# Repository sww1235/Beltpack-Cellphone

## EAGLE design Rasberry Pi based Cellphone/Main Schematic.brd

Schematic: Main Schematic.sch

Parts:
5VBOOST: Value; RSA0016B
ADC/DAC: SGTL5000_32QFN; QFN32
BATT: JST_2PIN-SMT-RA; JST-PH-2-SMT-RA
BATTERY_CHARGER: MCP73871-2CCI/ML; QFN50P400X400X100-21N
C1: 1uF; C0402
C2: 4700uF/10V; R/2012-12R
C3, C16, C49, C50, C51, C52: 10uF/6.3V; R/2012-12R
C4: 10uF/10V; C0402K
C5, C6: 10uF; C0402K
C7: 01uF; C0402K
C8: 2.2uF; C0402K
C9, C10, C21, C22: 100uF; C0402K
C11, C12, C13, C18, C23, C24, C25, C28, C29, C30, C53, C54, C55, C56, C57, C58: 0.1uF/16V; R/2012-12R
C14, C15: 560pF/50V; R/2012-12R
C17, C33: 22uF/6.3V; R/2012-12R
C19, C31, C32, C34, C39, C40, C41, C42: 1uF; C0402K
C20: 1uF/6.3V; R/2012-12R
C26, C27: 8pF/50V; R/2012-12R
C35, C36, C37, C38, C43, C44: 10uF; R/2012-12R
C45, C46, C47, C48: 10nF/25V; C0402
C59, C61, C62, C63, C69, C71, C72, C73, C74, C79, C81, C82, C83, C84, C89, C91, C92, C93, C98, C99, C100, C101, C102, C104, C105, C106, C107, C108, C109, C110, C111, C112, C117, C118, C119, C120, C121, C122, C123, C124, C125, C126, C127: 0.1uF; C0402
C60, C67, C70, C75, C78, C80, C85, C88, C90, C94, C95, C96, C97, C103, C113, C114, C115, C116: 0.001uF; C0402
C66, C76, C86: 1.0uF; C0402
C68, C77, C87: 0.01uF; C0402
CHRG/LBO: ORANGE; CHIP-LED0603
D1, D2: DIODESOD-123; SOD-123
D3: RB521CS-30; SMB
DONE: GREEN; CHIP-LED0603
ETHERNET: EZG-2K-308 (Cat6A Rated); EZG-1B-1K-310
EXT_POWER_IN: EZG-2K-302; EZG-2B-2K-302
EXT_RADIO_INTERFACE: EZG-0K-309; EZG-0B-0K-309
GPIOA: EZG-2K-314; EZG-2B-2K-314
GPIOB: EZG-2K-314; EZG-2B-2K-314
HDMI: 47630-1012
HEADSET: EZG-2K-305; EZG-2B-2K-305
J1: Main B2B Header; DF40C-80DS
J2: Second B2B Header; DF40C-80DS
J3: Third B2B Header; DF40C-70DS
L1: 6.8uH; L2825P
L2: 1.5uH; L2825P
L3: BLM15PX121SN1; 0402
L4, L5, L6, L7, L8, L10, L11: 1000@100MHz; FB402
LT1085: 5v; DDPAK-3
MICRO_SD: MICROSD
MSATA: 679105700
ON/OFF?: Potential Location for On Off Switch; EG1218
PCIE1, PCIE2: 679105700
PWR: RED; CHIP-LED0603
Q1: 20V P-Channel Mosfet; SOT-23
Q2: 12MHz; CTS406
R1: 270K; M0805
R2, R6: 100K; M0805
R3, R4, R5, R8, R9, R10, R13: 1K; M0805
R7: 2K; M0805
R11: 1.87M; M0805
R12: 200K; M0805
R14: 73.2K 1%; M0805
R15: 24.0K 1%; M0805
R16: 10k; M0805
R17, R18, R19, R20, R22: 2.2k; M0805
R21: 1kΩ; M0805
RESET: SPST_TACT-KMR2; KMR2
RN1: 1.5kΩ; RN8P-4R-CRA06S
RT1, RT3, RT4, RT5, RT6: 2.2K; M0805
RT2: 150K; M0805
RT7: 10K; M0805
RT8: 649; M0805
RT9: 2.2Ω; M0805
RT10, RT11: 22Ω; M0805
RT12: 1MΩ; M0805
RT13, RT14, RT17, RT18, RT21, RT22: 20Ω; M0805
RT15, RT16, RT19, RT20, RT23, RT24: 49.9Ω; M0805
RT25, RT26, RT27: 4.7kΩ; M0805
RT28: 1.6kΩ; M0805
SD2_VSELECT: 741G53DCT; DCT_R-PDSO-G8
SW1, SW2, SW3: SPST_TACT-KMR2; KMR2
THERM: 1X2-3.5MM
U7: XIO3130_ZHC_196; ZHC196
U$1: USB-PWR; USB-MINIB-THM-MOLEX-PWRONLY
U$2: 1V8 Regulator; SOT95P237X112-3N
U$3, U$4, U$5: ESD7004; UDFN10
U$6: MCP1702T-1502E/CB; SOT95P255X145-3N
U$7: MCP1700T-1502E/TT; SOT95P237X112-3N
UART_BUF_0, UART_BUF_1, UART_BUF_2: NLX2G16; UDFN6
USBCON_1: USB_1; PN87520
USBCON_OTG: USB_OTG; PN87520
USB_AUDIO_CODEC: PCM2904DB; SSOP28DB
USB_CURR_LIM: MIC2026-1YM; SOIC8
USB_HUB: USB Hub; TQFP48_7X7
VREG_1: +5V -> 3V2; SOP08
X1, X3: 5036-008-210-862; 5036_008_210_862

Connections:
1V5: C52.+, C59.1, C69.1, C79.1, C89.1, C102.1, C104.1, C105.1, C106.1, C107.1, C108.1, C109.1, C110.1, C111.1, C112.1, C113.1, C114.1, C115.1, C116.1, C117.1, C118.1, C119.1, C120.1, C121.1, C122.1, C123.1, C124.1, C125.1, C126.1, C127.1, L4.1, L5.1, L6.1, L7.1, L8.1, PCIE1.6, PCIE1.28, PCIE1.48, PCIE2.6, PCIE2.28, PCIE2.48, R18.2, U7.A4 (VDD15_2), U7.A13 (RSVD_3), U7.B2 (VDD15_3), U7.B3 (VDD15_4), U7.B7 (VDD15_5), U7.B10 (VDD15_7), U7.B12 (RSVD), U7.C5 (VDD15_6), U7.C11 (VDD15_8), U7.C13 (VDD15_9), U7.C14 (VDD15_10), U7.E13 (VDD15_11), U7.F1 (VDD15_7), U7.F2 (VDD15_8), U7.G13 (VDD15_12), U7.H3 (VDD15_9), U7.K4 (VDD15), U7.L14 (VDD15_13), U7.M1 (VDD15_2), U7.M2 (VDD15_3), U7.M11 (VDD15_14), U7.M12 (VDD15_15), U7.N8 (VDD15_4), U7.N10 (VDD15_16), U7.N13 (VDD15_17), U7.N14 (VDD15_18), U7.P3 (VDD15_5), U7.P4 (VDD15_6), U7.P14 (VDD15), U$7.2 (VOUT)
1V8: C18.+, SD2_VSELECT.6 (Y2), U$2.2 (VOUT)
3V2: ADC/DAC.5 (VDDA), ADC/DAC.20 (VDDIO), C12.-, C17.+, C23.-, C49.+, C51.+, C74.1, C84.1, C94.1, C95.1, C96.1, C97.1, C98.1, C99.1, C100.1, C101.1, GPIOA.1, GPIOB.1, J1.P$63, J1.P$65, J1.P$67, J1.P$69, L2.2, L3.1, L10.1, L11.1, MSATA.2, MSATA.24, MSATA.39, MSATA.41, MSATA.52, PCIE1.2, PCIE1.24, PCIE1.39, PCIE1.41, PCIE1.52, PCIE2.2, PCIE2.24, PCIE2.39, PCIE2.41, PCIE2.52, Q1.2 (S), R14.1, R16.2, R19.1, R20.1, R21.2, R22.1, RT5.2, SD2_VSELECT.7 (Y1), SD2_VSELECT.8 (VCC), U7.A3 (VDD33_2), U7.A11 (VDD33_4), U7.B4 (VDD33), U7.D4 (RSVD), U7.D12 (VDD33_5), U7.K12 (VDD33_6), U7.M4 (VDD33_2), U7.N1 (VDD33_3), U7.P11 (VDD33), U$2.3 (VIN), U$6.3 (VIN), U$7.3 (VIN), UART_BUF_0.P$5 (VCC), UART_BUF_1.P$5 (VCC), UART_BUF_2.P$5 (VCC), USB_HUB.23 (FIX_PORT4), USB_HUB.34 (VCC_D), USB_HUB.37 (SELFPWR), USB_HUB.38 (VCC_D_2)
12C3_SDA: GPIOB.3
+5V: 5VBOOST.1 (VOUT_2), 5VBOOST.15 (VOUT_3), 5VBOOST.16 (VOUT), C3.+, C8.1, C9.1, C10.1, C16.+, C33.+, C34.1, GPIOA.2, GPIOB.2, HDMI.P$18, J1.P$71, J1.P$73, J1.P$75, J1.P$77, J1.P$79, R11.2, RT9.2, USB_CURR_LIM.7 (IN), VREG_1.4 (VIN)
AGNDX: USB_AUDIO_CODEC.22 (AGNDX)
AUD5_RXD: ADC/DAC.25 (I2S_DOUT), J2.P$57
AUD5_TXC: ADC/DAC.24 (I2S_SCLK), J2.P$51
AUD5_TXD: ADC/DAC.26 (I2S_DIN), J2.P$53
AUD5_TXFS: ADC/DAC.23 (I2S_LRCLK), J2.P$55
BOOT_MODE0: J3.P$3
BOOT_MODE1: J3.P$5
CCM_CLKO1: ADC/DAC.21 (SYS_MCLK), J2.P$59
CCM_CLKO2: J2.P$63
CLK1_N: C57.-, J2.P$3
CLK1_P: C58.-, J2.P$1
CSI_CLK0P: J2.P$13
CSI_D0M: J2.P$8
CSI_D0P: J2.P$10
CSI_D1M: J2.P$14
CSI_D1P: J2.P$16
CSI_D2M: J2.P$20
CSI_D2P: J2.P$22
CSI_D3M: J2.P$26
CSI_D3P: J2.P$28
DI1_D0_CS: J3.P$45
DI1_D1_CS: J3.P$49
DI1_DISP_CLK: J3.P$54
DI1_PIN01: J3.P$53
DI1_PIN02: J3.P$41
DI1_PIN03: J3.P$51
DI1_PIN15: J3.P$43
DISP1_DATA00: EXT_RADIO_INTERFACE.3, J1.P$66
DISP1_DATA01: EXT_RADIO_INTERFACE.2, J1.P$60
DISP1_DATA02: GPIOB.8, J1.P$56
DISP1_DATA03: GPIOB.9, J1.P$54
DISP1_DATA04: GPIOB.10, J1.P$64
DISP1_DATA05: J1.P$62, RT28.2, U7.B1 (*UP_PERST)
DISP1_DATA06: GPIOB.11, J1.P$58
DISP1_DATA07: J3.P$70
DISP1_DATA08: J3.P$55
DISP1_DATA09: J3.P$60
DISP1_DATA10: J3.P$57
DISP1_DATA11: J3.P$68
DISP1_DATA12: J3.P$59
DISP1_DATA13: J3.P$64
DISP1_DATA14: J3.P$63
DISP1_DATA15: J3.P$62
DISP1_DATA16: J3.P$66
DISP1_DATA17: J3.P$69
DISP1_DATA18: J3.P$56
DISP1_DATA19: J3.P$67
DISP1_DATA20: J3.P$58
DISP1_DATA21: J3.P$40
DISP1_DATA22: J3.P$61
DISP1_DATA23: J3.P$65
DN1_PERST: PCIE1.22, RT27.2, U7.B5 (*DN1_PERST)
DN2_PERST: PCIE2.22, RT25.2, U7.A2 (*DN2_PERST)
DN3_PERST: RT26.2, U7.A1 (*DN3_PERST)
DSI_CLK0M: J2.P$44
DSI_CLK0P: J2.P$46
DSI_D0M: J2.P$38
DSI_D0P: J2.P$40
DSI_D1M: J2.P$32
DSI_D1P: J2.P$34
ECSPI2_MISO: GPIOA.4, J1.P$45
ECSPI2_MOSI: GPIOA.3, J1.P$47
ECSPI2_SCLK: GPIOA.5, J1.P$49
ECSPI2_SS0: GPIOA.6, J1.P$32
ECSPI2_SS1: GPIOA.7, J1.P$34
EIM_WAIT: J3.P$1
ETH_TCT: C1.1, ETHERNET.9, ETHERNET.10, J1.P$29
GNDC: C1.2
HDMI_CEC_C: D3.C, HDMI.P$13, U$5.P$10
HDMI_CLKM: J2.P$39, U$4.P$5
HDMI_CLKP: J2.P$37, U$4.P$4
HDMI_D0M: J2.P$33, U$4.P$2
HDMI_D0P: J2.P$31, U$4.P$1
HDMI_D1M: J2.P$27, U$3.P$5
HDMI_D1P: J2.P$25, U$3.P$4
HDMI_D2M: J2.P$21, U$3.P$2
HDMI_D2P: J2.P$19, U$3.P$1
HDMI_HPD: J2.P$49, U$5.P$5
HDMI_HPD_C: HDMI.P$19, U$5.P$6
HDMI_SCL_C: HDMI.P$15, U$5.P$9
HDMI_SDA_C: HDMI.P$16, U$5.P$7
HDMI_TX_CEC_LINE: J2.P$43, U$5.P$1
HDMI_TX_DDC_SCL: J2.P$45, U$5.P$2
HDMI_TX_DDC_SDA: J2.P$47, U$5.P$4
I2C1_SCL: ADC/DAC.29 (CTRL_CLK), J1.P$53, MSATA.30, U7.B14 (SCL)
I2C1_SDA: ADC/DAC.27 (CTRL_DATA), J1.P$51, MSATA.32, U7.D13 (SDA)
I2C3_SCL: GPIOB.4, J1.P$31
I2C3_SDA: J1.P$33
LED_10_100_LED_1000: J1.P$25
LED_ACT: J1.P$27
LOWVOLTAGE: 5VBOOST.12 (LBO)
LVDS0_CLK_N: J2.P$78
LVDS0_CLK_P: J2.P$80
LVDS0_TX0_N: J2.P$60
LVDS0_TX0_P: J2.P$62
LVDS0_TX1_N: J2.P$66
LVDS0_TX1_P: J2.P$68
LVDS0_TX2_N: J2.P$72
LVDS0_TX2_P: J2.P$74
LVDS0_TX3_N: J2.P$79
LVDS0_TX3_P: J2.P$77
MDI_TRXN0: ETHERNET.2, J1.P$19
MDI_TRXN1: ETHERNET.4, J1.P$13
MDI_TRXN2: ETHERNET.6, J1.P$7
MDI_TRXN3: ETHERNET.8, J1.P$1
MDI_TRXP0: ETHERNET.1, J1.P$21
MDI_TRXP1: ETHERNET.3, J1.P$15
MDI_TRXP2: ETHERNET.5, J1.P$9
MDI_TRXP3: ETHERNET.7, J1.P$3
MIC_IN: C24.-, HEADSET.2, RT6.1
MLB_CN: J3.P$19
MLB_CP: J3.P$17
MLB_DN: J3.P$27
MLB_DP: J3.P$25
MLB_SN: J3.P$23
MLB_SP: J3.P$21
MSATA_DISABLE: MSATA.20, PCIE1.20, PCIE2.20, R16.1
MUTE/PWR_DOWN: RN1.5 (2), RN1.6 (2), RN1.7 (2), USB_AUDIO_CODEC.28 (!SSPND)
MX6_ONOFF: J3.P$13
unnamed: D1.A, EXT_POWER_IN.2
unnamed: D1.C, LT1085.3 (VIN)
unnamed: BATTERY_CHARGER.6 (*PG), PWR.C
unnamed: D2.A, U$1.VBUS
unnamed: BATTERY_CHARGER.2 (VPCC), R1.1, R2.2
unnamed: PWR.A, R3.2
unnamed: L2.1, VREG_1.5 (LX)
unnamed: CHRG/LBO.A, R5.2
unnamed: BATTERY_CHARGER.7 (STAT2), DONE.C
unnamed: DONE.A, R4.2
unnamed: BATTERY_CHARGER.8 (STAT1/*LBO), CHRG/LBO.C
unnamed: BATT.1 (2), BATTERY_CHARGER.14 (VBAT), BATTERY_CHARGER.15 (VBAT_2), BATTERY_CHARGER.16 (VBAT_SENSE), C6.1
unnamed: BATTERY_CHARGER.12 (PROG3), R6.2
unnamed: BATTERY_CHARGER.13 (PROG1), R7.2
unnamed: 5VBOOST.11 (EN), ON/OFF?.P
unnamed: BATTERY_CHARGER.5 (THERM), R8.2
unnamed: R8.1, RT2.2, THERM.1
unnamed: ADC/DAC.30 (VDDD), C11.-
unnamed: R14.2, R15.1, VREG_1.7 (FB)
unnamed: 5VBOOST.9 (LBI), R9.2, R10.1
unnamed: ADC/DAC.15 (MIC), C24.+
unnamed: 5VBOOST.3 (SW_2), 5VBOOST.4 (SW), L1.2
unnamed: 5VBOOST.14 (FB), R11.1, R12.2
unnamed: ADC/DAC.10 (VAG), C13.-
unnamed: C15.+, VREG_1.2 (SS)
unnamed: D3.A, RT5.1
unnamed: R13.1, VREG_1.1 (COMP)
unnamed: C14.+, R13.2
unnamed: ADC/DAC.2 (HP_R), C21.1
unnamed: ADC/DAC.6 (HP_L), C22.1
unnamed: ADC/DAC.16 (MIC_BIAS), C25.-, RT6.2
unnamed: C40.1, USB_AUDIO_CODEC.23 (VCCXI)
unnamed: C41.1, USB_AUDIO_CODEC.19 (VCCP2I)
unnamed: RT8.1, USB_HUB.11 (RREF)
unnamed: RT7.1, USB_HUB.39 (GANG)
unnamed: RT9.1, USB_AUDIO_CODEC.3 (VBUS)
unnamed: RT11.1, USB_AUDIO_CODEC.2 (D-)
unnamed: RT10.1, USB_AUDIO_CODEC.1 (D+)
unnamed: C33.-, USB_CURR_LIM.6 (GND)
unnamed: C35.+, USB_AUDIO_CODEC.10 (VCCCI)
unnamed: C36.+, EXT_RADIO_INTERFACE.4, EXT_RADIO_INTERFACE.7, USB_AUDIO_CODEC.14 (VCOM)
unnamed: C42.1, USB_AUDIO_CODEC.17 (VCCP1I)
unnamed: C38.+, USB_AUDIO_CODEC.12 (VINL)
unnamed: C37.+, USB_AUDIO_CODEC.13 (VINR)
unnamed: C38.-, EXT_RADIO_INTERFACE.9
unnamed: C37.-, EXT_RADIO_INTERFACE.8
unnamed: C43.-, EXT_RADIO_INTERFACE.6
unnamed: C44.-, EXT_RADIO_INTERFACE.5
unnamed: C43.+, USB_AUDIO_CODEC.15 (VOUTR)
unnamed: C44.+, USB_AUDIO_CODEC.16 (VOUTL)
unnamed: C45.1, MSATA.23
unnamed: SW3.1, SW3.3 (P1), USB_AUDIO_CODEC.5 (HID0)
unnamed: SW2.1, SW2.3 (P1), USB_AUDIO_CODEC.6 (HID1)
unnamed: RN1.2 (1), SW1.2 (S), SW1.4 (S1)
unnamed: SW1.1, SW1.3 (P1), USB_AUDIO_CODEC.7 (HID2)
unnamed: C39.1, RN1.8 (2), USB_AUDIO_CODEC.8 (SEL0), USB_AUDIO_CODEC.9 (SEL1), USB_AUDIO_CODEC.27 (VDDI)
unnamed: RN1.3 (1), SW2.2 (S), SW2.4 (S1)
unnamed: RN1.4 (1), SW3.2 (S), SW3.4 (S1)
unnamed: C46.1, MSATA.25
unnamed: C47.1, MSATA.31
unnamed: C48.1, MSATA.33
unnamed: C54.-, PCIE2.31
unnamed: C53.-, PCIE2.33
unnamed: C56.-, PCIE1.31
unnamed: C55.-, PCIE1.33
unnamed: C57.+, U7.L2 (UP_REFCKIN)
unnamed: C58.+, U7.L1 (UP_REFCKIP)
NVCC_SD2: C19.1, J1.P$61, SD2_VSELECT.1 (COM)
PCIE_RXM: J2.P$2, U7.J2 (UP_PERN)
PCIE_RXM1: PCIE1.23, U7.B6 (DN1_PERN)
PCIE_RXM2: PCIE2.23, U7.F14 (DN2_PERN)
PCIE_RXM3: U7.P9 (DN3_PERN)
PCIE_RXP: J2.P$4, U7.J1 (UP_PERP)
PCIE_RXP1: PCIE1.25, U7.A6 (DN1_PERP)
PCIE_RXP2: PCIE2.25, U7.F13 (DN2_PERP)
PCIE_RXP3: U7.N9 (DN3_PERP)
PCIE_TXM: J2.P$7, U7.G2 (UP_PETN)
PCIE_TXM1: C56.+, U7.B8 (DN1_PETN)
PCIE_TXM2: C54.+, U7.H14 (DN2_PETN)
PCIE_TXM3: U7.P7 (DN3_PETN)
PCIE_TXP: J2.P$9, U7.A8 (DN1_PETP), U7.G1 (UP_PETP)
PCIE_TXP1: C55.+
PCIE_TXP2: C53.+, U7.H13 (DN2_PETP)
PCIE_TXP3: U7.N7 (DN3_PETP)
PE: 5VBOOST.5 (PGND_2), 5VBOOST.6 (PGND_3), 5VBOOST.7 (PGND), 5VBOOST.10 (SYNC), 5VBOOST.13 (GND), 5VBOOST.17 (PAD), ADC/DAC.1 (GND), ADC/DAC.3 (GND2), ADC/DAC.7 (AGND), ADC/DAC.31 (CTRL_ADR0_CS), ADC/DAC.32 (CTRL_MODE), ADC/DAC.EXP (GND), BATT.2 (1), BATTERY_CHARGER.10 (VSS), BATTERY_CHARGER.11 (VSS_2), BATTERY_CHARGER.21 (EP), C2.-, C3.-, C4.2, C5.2, C6.2, C7.2, C8.2, C9.2, C10.2, C11.+, C12.+, C13.+, C14.-, C15.-, C16.-, C17.-, C18.-, C19.2, C20.-, C23.+, C25.+, C26.-, C27.-, C28.-, C29.-, C30.-, C31.2, C32.2, C34.2, C35.-, C36.-, C39.2, C40.2, C41.2, C42.2, C49.-, C50.-, C51.-, C52.-, C59.2, C60.2, C61.2, C62.2, C63.2, C66.2, C67.2, C68.2, C69.2, C70.2, C71.2, C72.2, C73.2, C74.2, C75.2, C76.2, C77.2, C78.2, C79.2, C80.2, C81.2, C82.2, C83.2, C84.2, C85.2, C86.2, C87.2, C88.2, C89.2, C90.2, C91.2, C92.2, C93.2, C94.2, C95.2, C96.2, C97.2, C98.2, C99.2, C100.2, C101.2, C102.2, C103.2, C104.2, C105.2, C106.2, C107.2, C108.2, C109.2, C110.2, C111.2, C112.2, C113.2, C114.2, C115.2, C116.2, C117.2, C118.2, C119.2, C120.2, C121.2, C122.2, C123.2, C124.2, C125.2, C126.2, C127.2, EXT_POWER_IN.1, EXT_RADIO_INTERFACE.1, GPIOA.14, GPIOB.14, HDMI.P$2, HDMI.P$5, HDMI.P$8, HDMI.P$11, HDMI.P$17, HEADSET.1, HEADSET.3, J1.P$2, J1.P$5, J1.P$8, J1.P$11, J1.P$14, J1.P$17, J1.P$20, J1.P$23, J1.P$26, J1.P$35, J1.P$36, J1.P$70, J1.P$72, J1.P$74, J1.P$76, J1.P$78, J1.P$80, J2.P$5, J2.P$6, J2.P$11, J2.P$12, J2.P$17, J2.P$18, J2.P$23, J2.P$24, J2.P$29, J2.P$30, J2.P$35, J2.P$36, J2.P$48, J2.P$58, J2.P$61, J2.P$64, J2.P$70, J2.P$75, J3.P$10, J3.P$16, J3.P$30, J3.P$33, J3.P$47, J3.P$52, LT1085.1 (GND), LT1085.THERM (GND), MICRO_SD.6 (VSS), MICRO_SD.MT1 (GND), MICRO_SD.MT2 (GND1), MSATA.4, MSATA.9, MSATA.15, MSATA.18, MSATA.21, MSATA.26, MSATA.27, MSATA.29, MSATA.34, MSATA.35, MSATA.37, MSATA.40, MSATA.43, MSATA.50, ON/OFF?.O, PCIE1.4, PCIE1.9, PCIE1.15, PCIE1.18, PCIE1.21, PCIE1.26, PCIE1.27, PCIE1.29, PCIE1.34, PCIE1.35, PCIE1.37, PCIE1.40, PCIE1.43, PCIE1.50, PCIE2.4, PCIE2.9, PCIE2.15, PCIE2.18, PCIE2.21, PCIE2.26, PCIE2.27, PCIE2.29, PCIE2.34, PCIE2.35, PCIE2.37, PCIE2.40, PCIE2.43, PCIE2.50, R2.1, R6.1, R7.1, R10.2, R12.1, R15.2, R17.1, R18.1, RESET.3 (P1), RT1.2, RT2.1, RT3.1, RT4.1, RT7.2, RT8.2, RT15.2, RT16.2, RT19.2, RT20.2, RT23.2, RT24.2, RT25.1, RT26.1, RT27.1, RT28.1, SD2_VSELECT.2 (INH), SD2_VSELECT.3 (GND), SD2_VSELECT.4 (GND), THERM.2, U7.A5 (VSSA_2), U7.A10 (VSSA_8), U7.C4 (RSVD_2), U7.C7 (VSSA_3), U7.C8 (VSSA_4), U7.C9 (VSSA_5), U7.C10 (DN1_DPSTRP), U7.D1 (VSSD_REF), U7.D5 (VSS_2), U7.D6 (VSS_3), U7.D10 (VSS_3), U7.D11 (VSS_4), U7.E4 (VSSA_REF), U7.E5 (VSS_4), U7.E6 (VSS_5), U7.E7 (VSS_6), U7.E8 (VSS_7), U7.E9 (VSS_8), U7.E10 (VSS_5), U7.E11 (VSS_6), U7.E12 (VSS_7), U7.E14 (VSSA_9), U7.F5 (VSS_9), U7.F6 (VSS_10), U7.F7 (VSS_11), U7.F8 (VSS_12), U7.F9 (VSS_13), U7.F10 (VSS_8), U7.F11 (VSSA_10), U7.F12 (VSSA_11), U7.G3 (VSSA_6), U7.G5 (VSS_14), U7.G6 (VSS_15), U7.G7 (VSS_16), U7.G8 (VSS_17), U7.G9 (VSS_18), U7.G10 (VSS_9), U7.G14 (VSSA_12), U7.H1 (VSSA_7), U7.H5 (VSS_19), U7.H6 (VSS_20), U7.H7 (VSS_21), U7.H8 (VSS_22), U7.H9 (VSS_23), U7.H10 (VSS_10), U7.H12 (VSSA_13), U7.J5 (VSS_24), U7.J6 (VSS_25), U7.J7 (VSS_26), U7.J8 (VSS_27), U7.J9 (VSS_28), U7.J10 (VSS_11), U7.J13 (VSSA_14), U7.K1 (VSSA), U7.K2 (VSS_29), U7.K5 (VSS_30), U7.K6 (VSS_31), U7.K7 (VSS_32), U7.K8 (VSS_33), U7.K9 (VSS_34), U7.K10 (VSS_12), U7.K11 (VSS_13), U7.K13 (VSSA_15), U7.L4 (VSS_35), U7.L5 (VSS), U7.L9 (VSSA_2), U7.L10 (VSS_14), U7.L11 (VSS), U7.L13 (DN2_DPSTRP), U7.M5 (VSS_2), U7.M7 (VSSA_3), U7.M9 (VSSA_4), U7.N4 (DN3_DPSTRP), U7.N5 (VSSA_5), U7.N6 (VSSA_6), U7.P1 (RSVD_2), U7.P8 (VSSA_7), U7.P10 (VSSA), U$1.GND, U$2.1 (GND), U$3.P$3 (GND), U$3.P$8 (GND2), U$4.P$3 (GND), U$4.P$8 (GND2), U$5.P$3 (GND), U$5.P$8 (GND2), U$6.1 (GND), U$7.1 (GND), UART_BUF_0.P$2 (GND), UART_BUF_1.P$2 (GND), UART_BUF_2.P$2 (GND), USBCON_1.4, USBCON_OTG.4, USB_AUDIO_CODEC.4 (DGNDU), USB_AUDIO_CODEC.11 (AGNDC), USB_AUDIO_CODEC.18 (AGNDP), USB_AUDIO_CODEC.24 (TEST0), USB_AUDIO_CODEC.26 (DGND), USB_HUB.2 (GND), USB_HUB.8 (GND_2), USB_HUB.13 (GND_3), USB_HUB.20 (GND_4), VREG_1.P$1 (GND), X1.C3, X3.C3
PMIC_ON_REQ: J3.P$15
PMIC_STBY_REQ: J3.P$9
POR_B: J2.P$65, MSATA.22, RESET.4 (S1), USB_HUB.26 (RESET#)
PWM1_OUT: J1.P$68
PWM2_OUT: J1.P$41, Q1.1 (G), RT3.2
PWM3_OUT: J1.P$55
PWM4_OUT: J1.P$57
REFCLKN_1: PCIE1.11, RT14.2, RT16.1
REFCLKN_1_R: RT14.1, U7.B9 (DN1_REFCK_ON)
REFCLKN_2: PCIE2.11, RT22.2, RT24.1
REFCLKN_2_R: RT22.1, U7.J14 (DN2_REFCKON)
REFCLKN_3: RT18.2, RT20.1
REFCLKN_3_R: RT18.1, U7.P6 (DN3_REFCKON)
REFCLKP_1: PCIE1.13, RT13.2, RT15.1
REFCLKP_1_R: RT13.1, U7.A9 (DN1_REFCK_OP)
REFCLKP_2: PCIE2.13, RT21.2, RT23.1
REFCLKP_2_R: RT21.1, U7.K14 (DN2_REFCKOP)
REFCLKP_3: RT17.2, RT19.1
REFCLKP_3_R: RT17.1, U7.P5 (DN3_REFCKOP)
RXD0: GPIOA.9, R20.2, UART_BUF_0.P$3 (IN_A2)
RXD1: GPIOA.11, R19.2, UART_BUF_1.P$3 (IN_A2)
RXD2: GPIOA.13, R22.2, UART_BUF_2.P$3 (IN_A2)
SATA_RXN: C46.2, J1.P$6
SATA_RXP: C45.2, J1.P$4
SATA_TXN: C47.2, J1.P$10
SATA_TXP: C48.2, J1.P$12
SD2_CD_B: J1.P$50, MICRO_SD.CD1 (CARD_DETECT), MICRO_SD.CD2 (CARD_DETECT1)
SD2_CLK: J1.P$38, MICRO_SD.5 (SCLK)
SD2_CMD: J1.P$40, MICRO_SD.3 (DATA_IN)
SD2_DATA0: J1.P$42, MICRO_SD.7 (DATA_OUT)
SD2_DATA1: J1.P$44, MICRO_SD.8 (DAT1)
SD2_DATA2: J1.P$46, MICRO_SD.1 (DAT2)
SD2_DATA3: J1.P$48, MICRO_SD.2 (CS)
SD2_VSELECT: J2.P$73, RT1.1, SD2_VSELECT.5 (A)
SD3_CLK: GPIOB.6, J1.P$37
SD3_CMD: GPIOB.7, J1.P$39
SD3_DATA0: J3.P$24
SD3_DATA1: J3.P$22
SD3_DATA2: J3.P$20
SD3_DATA3: J3.P$18
SD3_DATA4: J3.P$8
SD3_DATA5: J3.P$6
SD3_DATA6: J3.P$4
SD3_DATA7: J3.P$2
SD3_RST: J3.P$26
SD3_VSELECT: J3.P$28
SD4_CLK: J3.P$32
SD4_CMD: J3.P$34
SD4_DATA0: J3.P$36
SD4_DATA3: J3.P$38
SPDIF_IN: J3.P$35
SPDIF_OUT: J2.P$50
STEREO_OUT_L: C22.2, HEADSET.4
STEREO_OUT_R: C21.2, HEADSET.5
TAMPER: J3.P$7
TMDS0+_C: HDMI.P$7, U$4.P$10
TMDS0-_C: HDMI.P$9, U$4.P$9
TMDS1+_C: HDMI.P$4, U$3.P$7
TMDS1-_C: HDMI.P$6, U$3.P$6
TMDS2+_C: HDMI.P$1, U$3.P$10
TMDS2-_C: HDMI.P$3, U$3.P$9
TMDSCLK+_C: HDMI.P$10, U$4.P$7
TMDSCLK-_C: HDMI.P$12, U$4.P$6
TXD0: GPIOA.8, UART_BUF_0.P$6 (OUT_Y1)
TXD1: GPIOA.10, UART_BUF_1.P$6 (OUT_Y1)
TXD2: GPIOA.12, UART_BUF_2.P$6 (OUT_Y1)
UART1_RX_DATA: J2.P$54, UART_BUF_0.P$4 (OUT_Y2)
UART1_TX_DATA: J2.P$52, UART_BUF_0.P$1 (IN_A1)
UART2_CTS_B: J3.P$48
UART2_RTS_B: J3.P$50
UART2_RX_DATA: J3.P$44, UART_BUF_1.P$4 (OUT_Y2)
UART2_TX_DATA: J3.P$46, UART_BUF_1.P$1 (IN_A1)
UART3_RX_DATA: J3.P$31, UART_BUF_2.P$4 (OUT_Y2)
UART3_TX_DATA: J3.P$29, UART_BUF_2.P$1 (IN_A1)
UIM_AUX1_1: X3.C6
UIM_AUX1_2: X1.C6
UIM_AUX2_1: X3.C8
UIM_AUX2_2: X1.C8
UIM_CLK_1: PCIE1.12, X3.C2
UIM_CLK_2: PCIE2.12, X1.C2
UIM_DATA_1: PCIE1.10, X3.C4
UIM_DATA_2: PCIE2.10, X1.C4
UIM_PWR_1: PCIE1.8, X3.C1
UIM_PWR_2: PCIE2.8, X1.C1
UIM_RST_1: PCIE1.14, X3.C5
UIM_RST_2: PCIE2.14, X1.C5
UIM_VPP_1: PCIE1.16, X3.C7
UIM_VPP_2: PCIE2.16, X1.C7
USB_H1_OC: J2.P$69
USB_H1_PWR_EN: J1.P$28, USB_CURR_LIM.4 (ENB)
USB_H1_VBUS: J1.P$52, USBCON_1.1, USB_CURR_LIM.5 (OUTB)
USB_HOST_DN: J1.P$24, USB_HUB.3 (D-)
USB_HOST_DP: J1.P$22, USB_HUB.4 (D+)
USB_HUB_DN1: USBCON_1.2, USB_HUB.5 (DD-[1])
USB_HUB_DN2: PCIE1.36, USB_HUB.9 (DD-[2])
USB_HUB_DN3: PCIE2.36, USB_HUB.17 (DD-[3])
USB_HUB_DN4: RT11.2, USB_HUB.21 (DD-[4])
USB_HUB_DP1: USBCON_1.3, USB_HUB.6 (DD+[1])
USB_HUB_DP2: PCIE1.38, USB_HUB.10 (DD+[2])
USB_HUB_DP3: PCIE2.38, USB_HUB.18 (DD+[3])
USB_HUB_DP4: RN1.1, RT10.2, USB_HUB.22 (DD+[4])
USB_OTG_CHD_B: J2.P$71
USB_OTG_DN: J1.P$18, USBCON_OTG.2
USB_OTG_DP: J1.P$16, USBCON_OTG.3
USB_OTG_ID: GPIOB.5, J2.P$56
USB_OTG_OC: J2.P$67
USB_OTG_PWR_EN: J1.P$30, USB_CURR_LIM.1 (ENA)
USB_OTG_VBUS: J1.P$43, USBCON_OTG.1, USB_CURR_LIM.8 (OUTA)
VAUX33REF: R21.1, U7.E1 (VAUX33_REF)
VBAT: 5VBOOST.8 (VBAT), BATTERY_CHARGER.1 (OUT_2), BATTERY_CHARGER.20 (OUT), C5.1, C7.1, L1.1, ON/OFF?.S, R9.1
VCC: USB_HUB.47 (VCC)
VDD15REF: C103.1, L8.2, U7.F3 (VDD15_REF)
VDD33REF: C85.1, L11.2, U7.E2 (VDD33_REF)
VDDA15_0: C60.1, C61.1, C62.1, C63.1, L4.2, U7.G4 (VDDA15_6), U7.H2 (VDDA15_7), U7.H4 (VDDA15_8), U7.J4 (VDDA15_9), U7.K3 (VDDA15_10)
VDDA15_1: C70.1, C71.1, C72.1, C73.1, L5.2, U7.A7 (VDDA15_2), U7.D7 (VDDA15_3), U7.D8 (VDDA15_4), U7.D9 (VDDA15_5)
VDDA15_2: C80.1, C81.1, C82.1, C83.1, L6.2, U7.G11 (VDDA15_4), U7.G12 (VDDA15_5), U7.H11 (VDDA15_6), U7.J11 (VDDA15_7), U7.J12 (VDDA15)
VDDA15_3: C90.1, C91.1, C92.1, C93.1, L7.2, U7.L6 (VDDA15_11), U7.L7 (VDDA15_12), U7.L8 (VDDA15), U7.M6 (VDDA15_2), U7.M8 (VDDA15_3)
VDDA33F: C75.1, L10.2, U7.J3 (VDDA33)
VDDCOMB15: C86.1, C87.1, C88.1, U7.C1 (VDD_COMB15)
VDDCOMB33: C76.1, C77.1, C78.1, U7.F4 (VDD_COMB33)
VDDCOMBIO: C66.1, C67.1, C68.1, U7.D3 (VDD_COMBIO)
VIN+5VBATT: BATTERY_CHARGER.3 (SEL), BATTERY_CHARGER.4 (PROG2), BATTERY_CHARGER.9 (*TE), BATTERY_CHARGER.17 (CE), BATTERY_CHARGER.18 (IN_2), BATTERY_CHARGER.19 (IN), C2.+, C4.1, D2.C, LT1085.2 (VOUT), R1.2, R3.1, R4.1, R5.1
V_1V5: C50.+, MSATA.6, MSATA.28, MSATA.48, R17.2, U$6.2 (VOUT)
V_3V2_FLTR: C28.+, C29.+, C30.+, C31.1, C32.1, L3.2, USB_HUB.1 (VCC_A), USB_HUB.7 (VCC_A_2), USB_HUB.12 (VCC_A_3), USB_HUB.16 (VCC_A_4), USB_HUB.19 (VCC_A_5), USB_HUB.48 (VREG)
V_SD: C20.+, MICRO_SD.4 (VDD), Q1.3 (D), RT4.2
WDOG1_B: J3.P$42
XIN: C26.+, Q2.1, RT12.1, USB_AUDIO_CODEC.21 (XTI), USB_HUB.14 (XIN)
XOUT: C27.+, Q2.3 (2), RT12.2, USB_AUDIO_CODEC.20 (XTO), USB_HUB.15 (XOUT)

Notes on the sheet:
pcie bus
msata
1x stacked USB and HDMI Digital Coax S/PDIF LEDS Various Display connectors (Maybe leave off) RTC battery HEader MIPI CSI connector?
connect 10k thermistor here
connect low voltage to microcontroller to trigger low battery shutdown
Main Power feeds are +5V and 3V2
may need amplifiers here
Connect to amplifier if needed

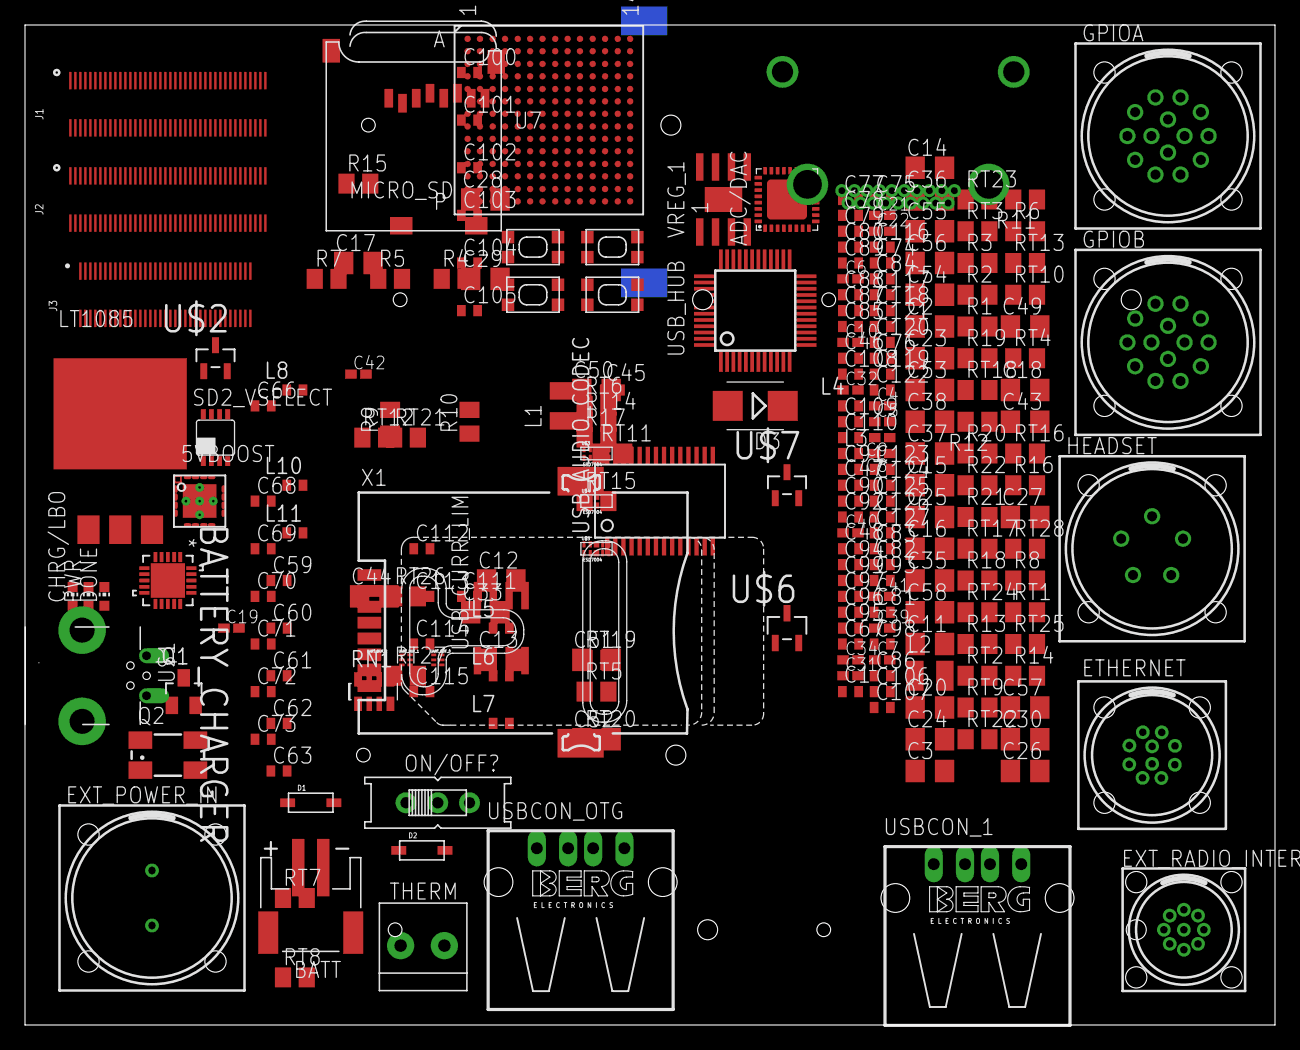
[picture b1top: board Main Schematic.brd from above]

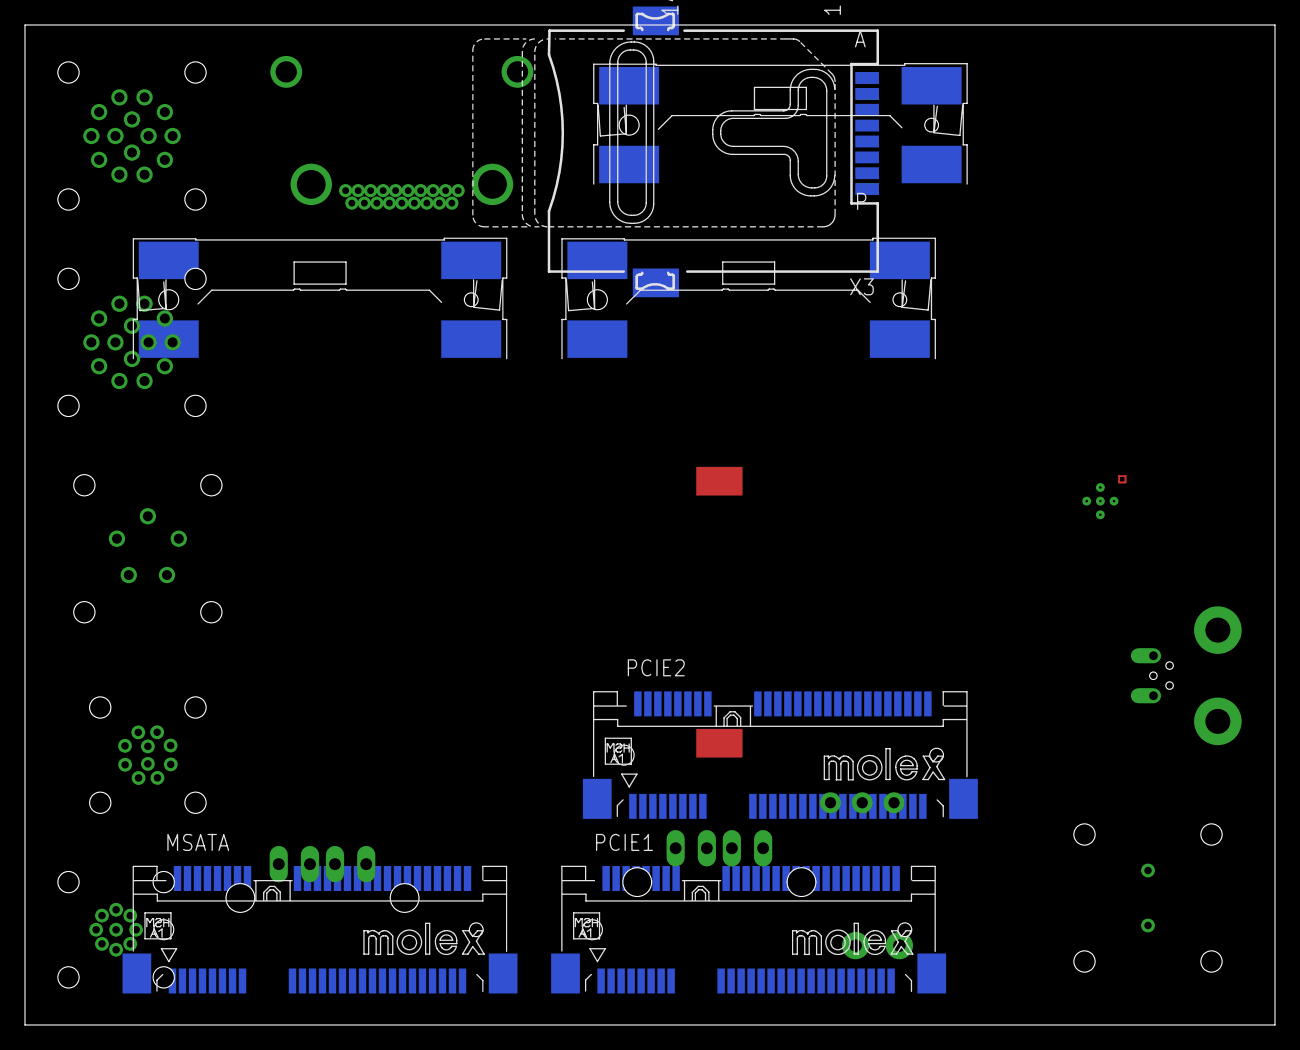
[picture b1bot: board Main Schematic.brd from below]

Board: 2 copper layers, 100.0 x 80.0 mm, 239 parts (4 on the bottom side), 232 nets, no tracks yet.

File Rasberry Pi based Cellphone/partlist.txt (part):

Partlist

Exported from Main Schematic.sch at 5/1/15 15:12

EAGLE Version 7.2.0 Copyright (c) 1988-2014 CadSoft

Assembly variant: 

Part                Value                                Device                     Package                     Library                        Sheet

5VBOOST             Value                                TPS61030RSAR               RSA0016B                    texas                          1
ADC/DAC             SGTL5000_32QFN                       SGTL5000                   QFN32                       freescale                      1
BATT                                                     JST_2PIN-SMT-RA            JST-PH-2-SMT-RA             adafruit                       1
BATTERY_CHARGER     MCP73871-2CCI/ML                     MCP73871-2CCI/ML           QFN50P400X400X100-21N       Microchip_By_element14_Batch_1 1
C1                  1uF                                  C-USC0402                  C0402                       adafruit                       1
C2                  4700uF/10V                           CPOL-USR/2012-12R          R/2012-12R                  adafruit                       1
C3                  10uF/6.3V                            CPOL-USR/2012-12R          R/2012-12R                  adafruit                       1
C4                  10uF/10V                             C-USC0402K                 C0402K                      adafruit                       1
C5                  10uF                                 C-USC0402K                 C0402K                      adafruit                       1
C6                  10uF                                 C-USC0402K                 C0402K                      adafruit                       1
C7                  01uF                                 C-USC0402K                 C0402K                      adafruit                       1
C8                  2.2uF                                C-USC0402K                 C0402K                      adafruit                       1
C9                  100uF                                C-USC0402K                 C0402K                      adafruit                       1
C10                 100uF                                C-USC0402K                 C0402K                      adafruit                       1
C11                 0.1uF/16V                            CPOL-USR/2012-12R          R/2012-12R                  adafruit                       1
C12                 0.1uF/16V                            CPOL-USR/2012-12R          R/2012-12R                  adafruit                       1
C13                 0.1uF/16V                            CPOL-USR/2012-12R          R/2012-12R                  adafruit                       1
C14                 560pF/50V                            CPOL-USR/2012-12R          R/2012-12R                  adafruit                       1
C15                 560pF/50V                            CPOL-USR/2012-12R          R/2012-12R                  adafruit                       1
C16                 10uF/6.3V                            CPOL-USR/2012-12R          R/2012-12R                  adafruit                       1
C17                 22uF/6.3V                            CPOL-USR/2012-12R          R/2012-12R                  adafruit                       1
C18                 0.1uF/16V                            CPOL-USR/2012-12R          R/2012-12R                  adafruit                       1
C19                 1uF                                  C-USC0402K                 C0402K                      adafruit                       1
C20                 1uF/6.3V                             CPOL-USR/2012-12R          R/2012-12R                  adafruit                       1
C21                 100uF                                C-USC0402K                 C0402K                      adafruit                       1
C22                 100uF                                C-USC0402K                 C0402K                      adafruit                       1
C23                 0.1uF/16V                            CPOL-USR/2012-12R          R/2012-12R                  adafruit                       1
C24                 0.1uF/16V                            CPOL-USR/2012-12R          R/2012-12R                  adafruit                       1
C25                 0.1uF/16V                            CPOL-USR/2012-12R          R/2012-12R                  adafruit                       1
C26                 8pF/50V                              CPOL-USR/2012-12R          R/2012-12R                  adafruit                       1
C27                 8pF/50V                              CPOL-USR/2012-12R          R/2012-12R                  adafruit                       1
C28                 0.1uF/16V                            CPOL-USR/2012-12R          R/2012-12R                  adafruit                       1
C29                 0.1uF/16V                            CPOL-USR/2012-12R          R/2012-12R                  adafruit                       1
C30                 0.1uF/16V                            CPOL-USR/2012-12R          R/2012-12R                  adafruit                       1
C31                 1uF                                  C-USC0402K                 C0402K                      adafruit                       1
C32                 1uF                                  C-USC0402K                 C0402K                      adafruit                       1
C33                 22uF/6.3V                            CPOL-USR/2012-12R          R/2012-12R                  adafruit                       1
C34                 1uF                                  C-USC0402K                 C0402K                      adafruit                       1
C35                 10uF                                 CPOL-USR/2012-12R          R/2012-12R                  adafruit                       1
C36                 10uF                                 CPOL-USR/2012-12R          R/2012-12R                  adafruit                       1
C37                 10uF                                 CPOL-USR/2012-12R          R/2012-12R                  adafruit                       1
C38                 10uF                                 CPOL-USR/2012-12R          R/2012-12R                  adafruit                       1
C39                 1uF                                  C-USC0402K                 C0402K                      adafruit                       1
C40                 1uF                                  C-USC0402K                 C0402K                      adafruit                       1
C41                 1uF                                  C-USC0402K                 C0402K                      adafruit                       1
C42                 1uF                                  C-USC0402K                 C0402K                      adafruit                       1
C43                 10uF                                 CPOL-USR/2012-12R          R/2012-12R                  adafruit                       1
C44                 10uF                                 CPOL-USR/2012-12R          R/2012-12R                  adafruit                       1
C45                 10nF/25V                             C-USC0402                  C0402                       adafruit                       1
C46                 10nF/25V                             C-USC0402                  C0402                       adafruit                       1
C47                 10nF/25V                             C-USC0402                  C0402                       adafruit                       1
C48                 10nF/25V                             C-USC0402                  C0402                       adafruit                       1
C49                 10uF/6.3V                            CPOL-USR/2012-12R          R/2012-12R                  adafruit                       1
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
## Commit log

2015-04-15 Adding Initial Files
2015-04-22 Adding Connectors
2015-04-22 Finished Wiring main b2b connectors
2015-04-24 Finished Power Supply and Battery Charger
2015-04-25 added audio, usband some more power stuff
2015-04-30 random commit
2015-05-01 almost finished schematic
2015-05-01 fixed some errors in schematic and made brd easier to look at
2015-07-18 adding txt version of description
2015-07-19 Create New Ideas for Connectors
    Change connectors with these ideas in mind
2015-07-23 Update New Ideas for Connectors
2015-07-24 removed backups
2015-07-24 adding extensions
2015-07-24 This is a commit message
